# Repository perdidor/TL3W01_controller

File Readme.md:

# Tarot TL3W01 360 degrees Three-axis adjustable stabilizing gimbal controller

## Problem description:

1. Device has only SBUS input

2. Original TL3W01 firmware will rotate camera until SBUS channel value returned to neutral. No updates provided from manufacturer. No one email message answered. OK here we go now.

## Solution

Hardware device with ATMEGA 644A chip, which converting 5 PWM inputs to single SBUS output. Additionally, it reads feedback from gimbal debug output and keeps camera direction constant relative to ground, according to PWM value (behavior could be customized).

PCB source is KiCAD 8.0 project.

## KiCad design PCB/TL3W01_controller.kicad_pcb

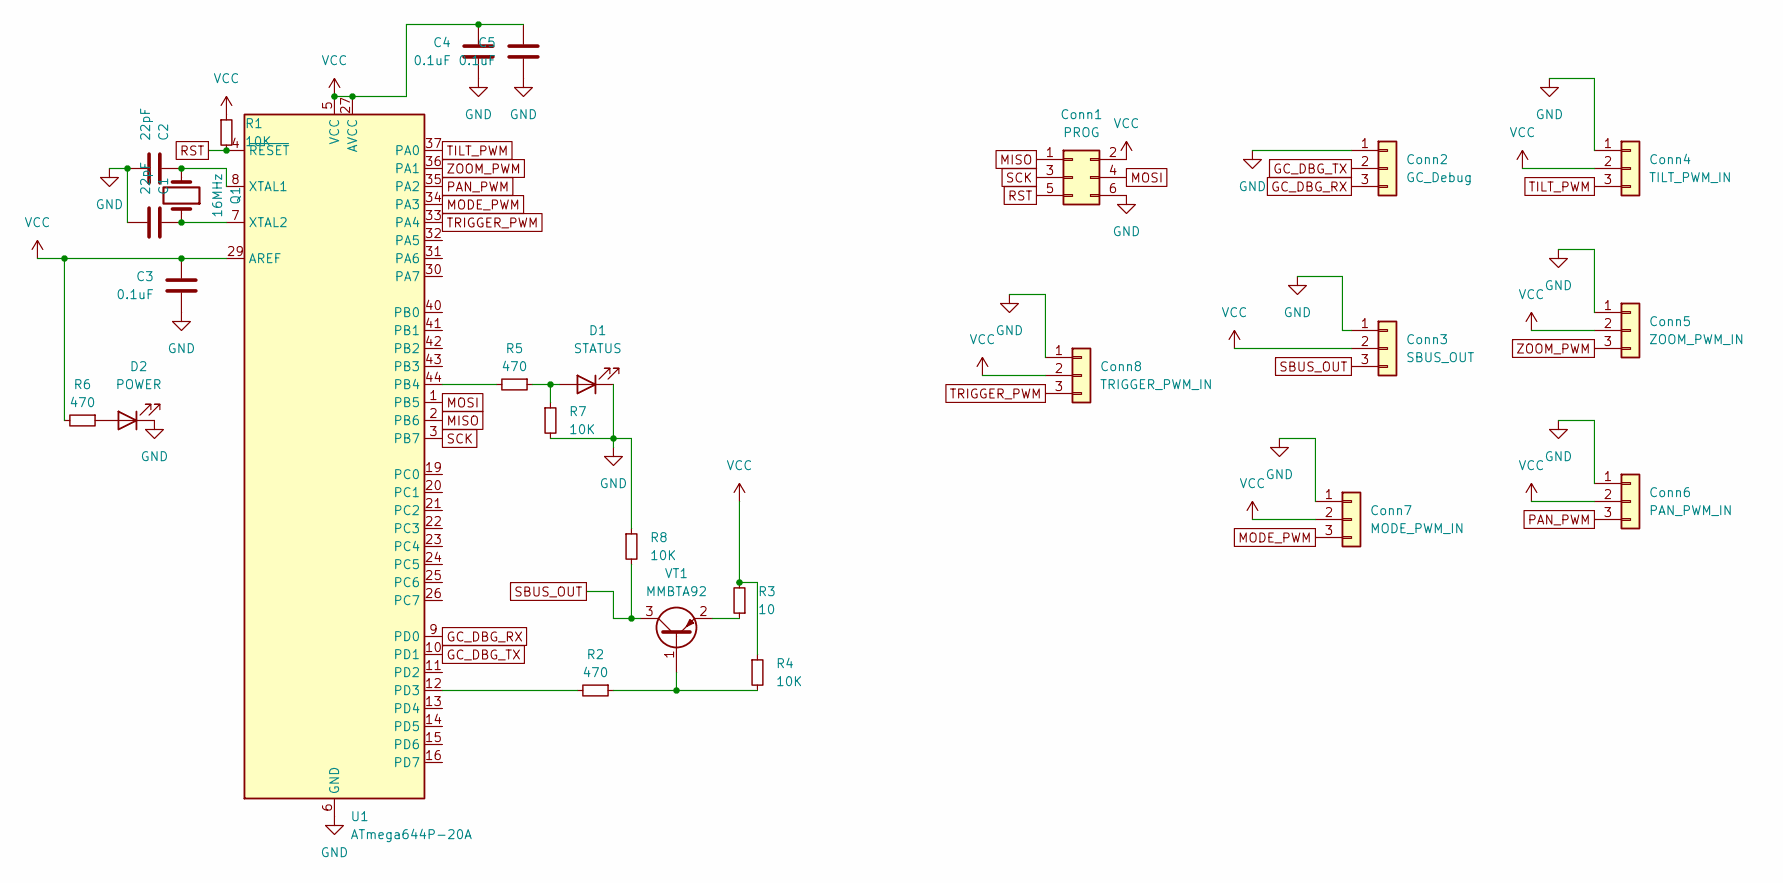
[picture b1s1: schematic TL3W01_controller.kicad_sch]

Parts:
C1, C2: 22pF; C_0805_2012Metric
C3, C4, C5: 0.1uF; C_0805_2012Metric
Conn1: PROG; PinHeader_2x03_P2.54mm_Horizontal
Conn2: GC_Debug; JST_GH_SM03B-GHS-TB_1x03-1MP_P1.25mm_Horizontal
Conn3: SBUS_OUT; PinHeader_1x03_P2.54mm_Horizontal
Conn4: TILT_PWM_IN; PinHeader_1x03_P2.54mm_Horizontal
Conn5: ZOOM_PWM_IN; PinHeader_1x03_P2.54mm_Horizontal
Conn6: PAN_PWM_IN; PinHeader_1x03_P2.54mm_Horizontal
Conn7: MODE_PWM_IN; PinHeader_1x03_P2.54mm_Horizontal
Conn8: TRIGGER_PWM_IN; PinHeader_1x03_P2.54mm_Horizontal
D1: STATUS; LED_0805_2012Metric
D2: POWER; LED_0805_2012Metric
Q1: 16MHz; Crystal_SMD_HC49-SD
R1, R4, R7, R8: 10K; R_0805_2012Metric
R2, R5, R6: 470; R_0805_2012Metric
R3: 10; R_0805_2012Metric
U1: ATmega644P-20A; TQFP-44_10x10mm_P0.8mm
VT1: MMBTA92; SOT-23

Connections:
GC_DBG_RX: Conn2.3, U1.9 (PD0)
GC_DBG_TX: Conn2.2, U1.10 (PD1)
GND: C1.2, C2.2, C3.1, C4.1, C5.1, Conn1.6 (GND), Conn2.1, Conn3.1, Conn4.1, Conn5.1, Conn6.1, Conn7.1, Conn8.1, D1.1 (K), D2.1 (K), R7.2, R8.1, U1.6 (GND), U1.18 (GND), U1.28 (GND), U1.39 (GND)
MISO: Conn1.1 (MISO), U1.2 (PB6)
MODE_PWM: Conn7.3, U1.34 (PA3)
MOSI: Conn1.4 (MOSI), U1.1 (PB5)
unnamed: D1.2 (A), R5.1, R7.1
unnamed: D2.2 (A), R6.1
unnamed: R5.2, U1.44 (PB4)
unnamed: R2.2, U1.12 (PD3)
unnamed: C2.1, Q1.2, U1.8 (XTAL1)
unnamed: C1.1, Q1.1, U1.7 (XTAL2)
unnamed: R2.1, R4.2, VT1.1 (B)
unnamed: R3.1, VT1.2 (E)
PAN_PWM: Conn6.3, U1.35 (PA2)
RST: Conn1.5 (RST), R1.2, U1.4 (~RESET)
SBUS_OUT: Conn3.3, R8.2, VT1.3 (C)
SCK: Conn1.3 (SCK), U1.3 (PB7)
TILT_PWM: Conn4.3, U1.37 (PA0)
TRIGGER_PWM: Conn8.3, U1.33 (PA4)
VCC: C3.2, C4.2, C5.2, Conn1.2 (VCC), Conn3.2, Conn4.2, Conn5.2, Conn6.2, Conn7.2, Conn8.2, R1.1, R3.2, R4.1, R6.2, U1.5 (VCC), U1.17 (VCC), U1.27 (AVCC), U1.29 (AREF), U1.38 (VCC)
ZOOM_PWM: Conn5.3, U1.36 (PA1)

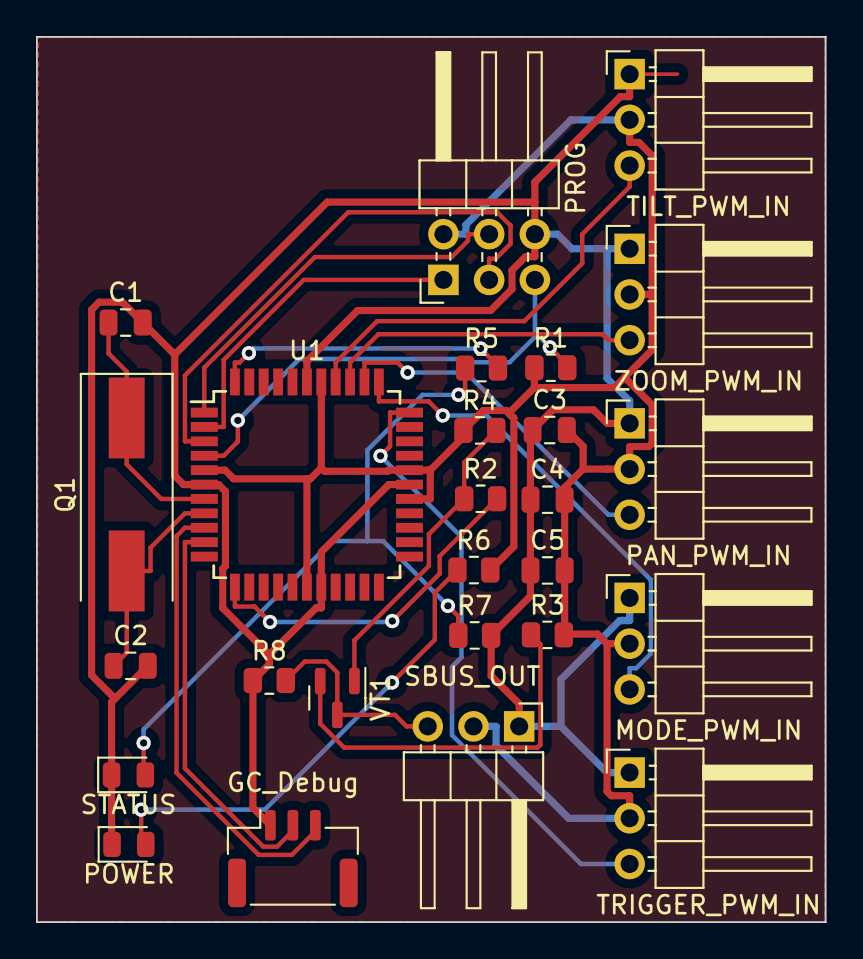
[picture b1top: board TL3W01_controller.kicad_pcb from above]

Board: 2 copper layers, 43.8 x 49.2 mm, 26 parts (0 on the bottom side), 22 nets.
